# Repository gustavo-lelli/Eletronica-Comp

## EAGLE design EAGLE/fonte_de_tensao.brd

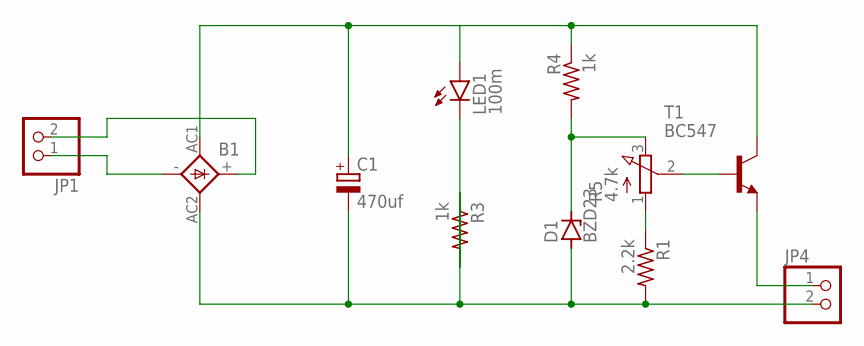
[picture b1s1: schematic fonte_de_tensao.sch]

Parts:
B1: 1KAB
C1: 470uf; E3,5-10
D1: BZD23; SOD81
JP1, JP4: PINHD-1X2; 1X02
LED1: 100m; LED5MM
R1: 2.2k; 0309/12
R3, R4: 1k; 0309/12
R5: 4.7k; 3RP/1610N
T1: BC547; TO92

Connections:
unnamed: B1.-, JP1.1
unnamed: JP4.1, T1.1 (E)
unnamed: B1.+, JP1.2
unnamed: B1.AC2, C1.-, D1.A, JP4.2, R1.2, R3.1
unnamed: B1.AC1, C1.+, LED1.A, R4.1, T1.3 (C)
unnamed: R1.1, R5.1 (A)
unnamed: LED1.K (C), R3.2
unnamed: D1.C, R4.2, R5.3 (E)
unnamed: R5.2 (S), T1.2 (B)

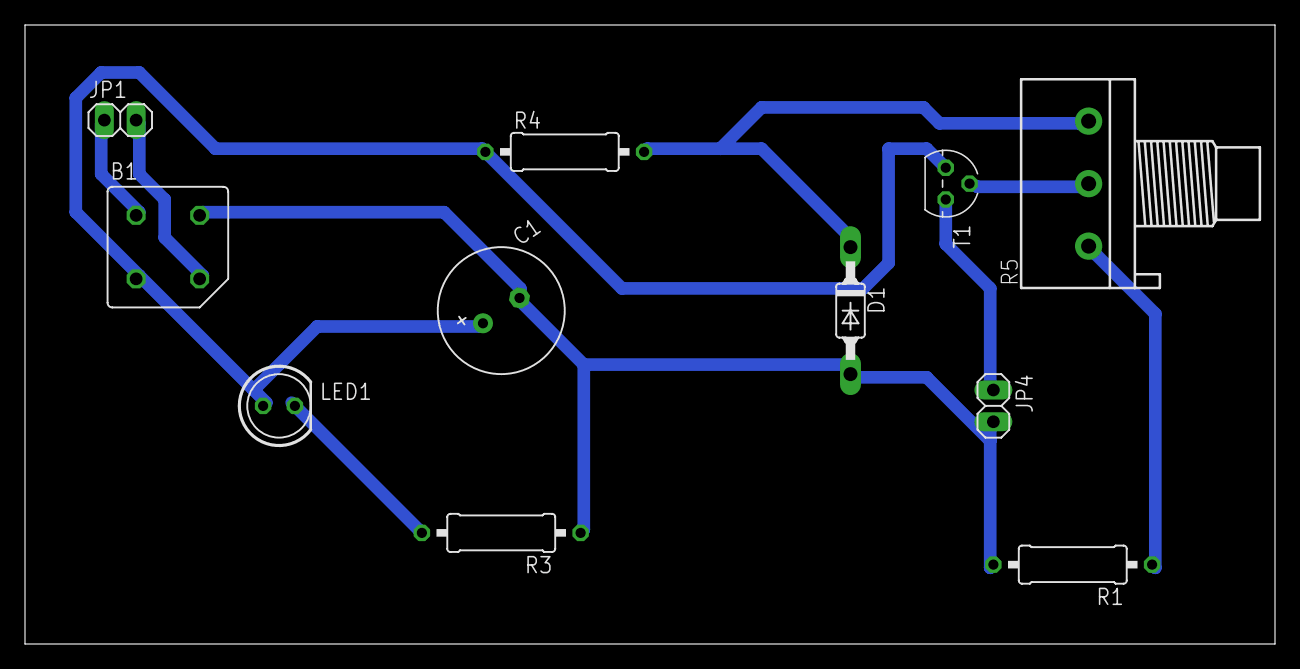
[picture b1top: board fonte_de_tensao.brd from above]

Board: 2 copper layers, 100.0 x 49.5 mm, 11 parts (0 on the bottom side), 9 nets.

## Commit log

2020-06-28 Create dsjkscncd
2020-06-28 Update dsjkscncd
2020-06-28 Create Slides
2020-06-29 Create Link para o Circuito no Falstad
2020-06-29 Update Link para o Circuito no Falstad
2020-06-29 Create teste
2020-06-30 Create Link para a Simluação
2020-06-30 Update Link para a Simluação
